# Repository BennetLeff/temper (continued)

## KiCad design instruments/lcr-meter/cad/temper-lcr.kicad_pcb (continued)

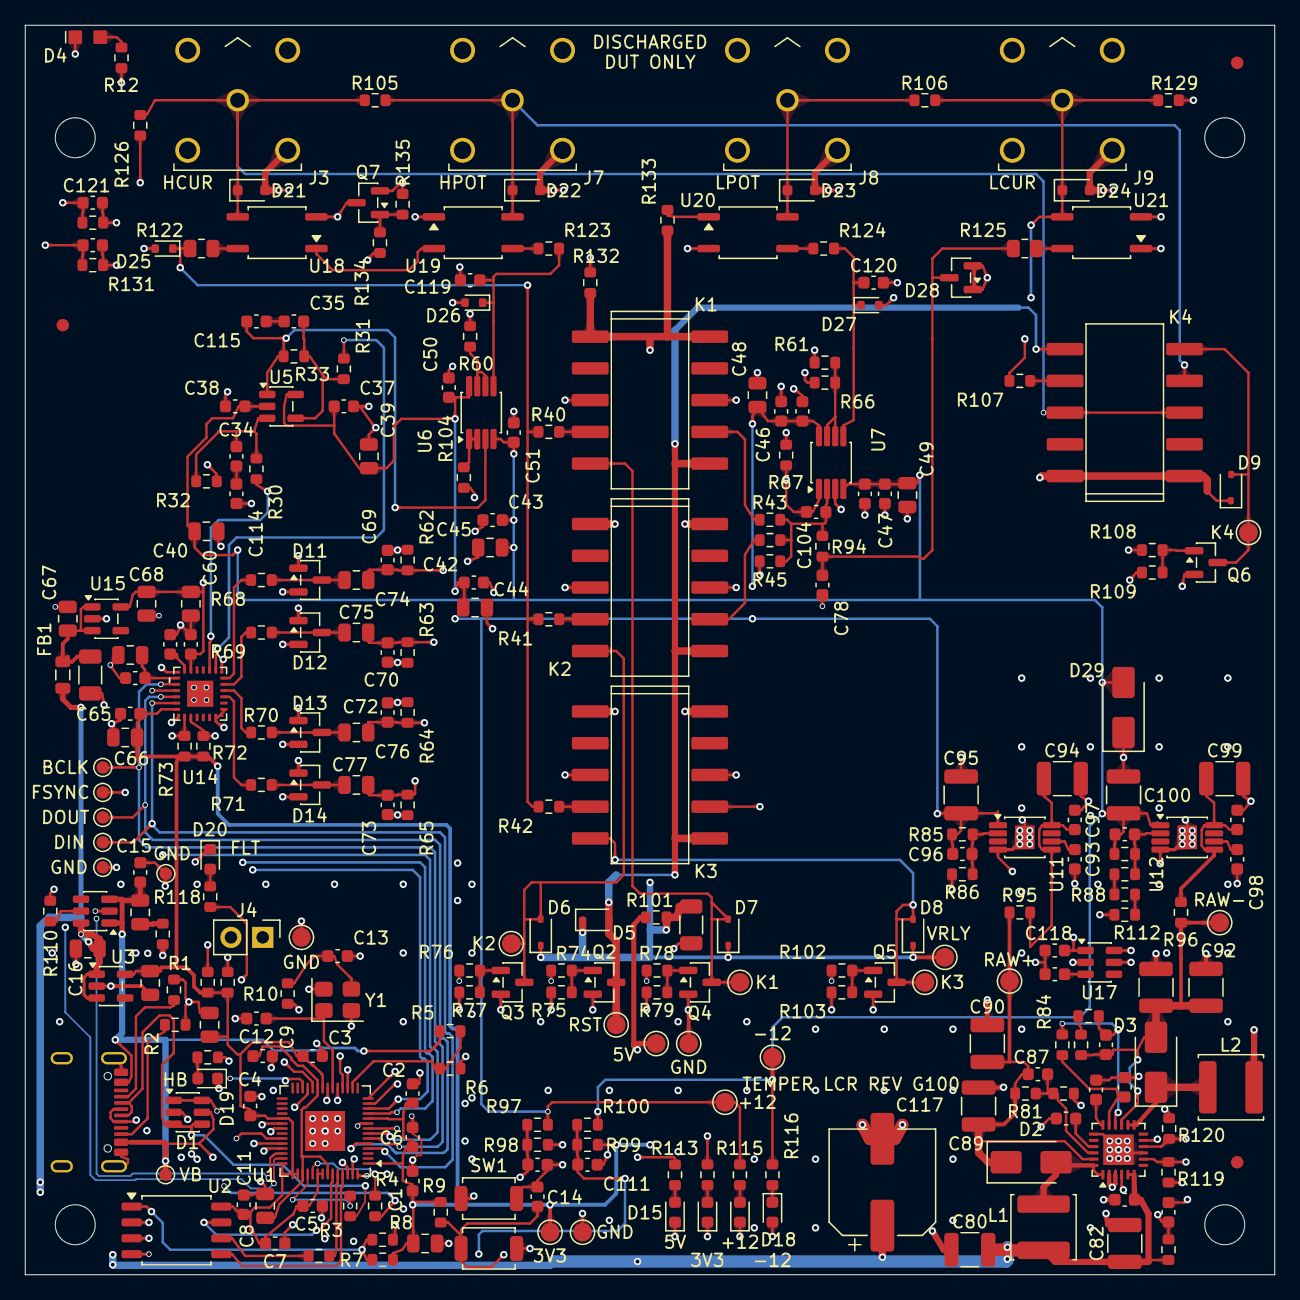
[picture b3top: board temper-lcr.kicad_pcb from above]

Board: 4 copper layers, 100.0 x 100.0 mm, 282 parts (0 on the bottom side), 143 nets.

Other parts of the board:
FID1, FID2, FID3: Fiducial_1mm_Mask2mm
H1, H2, H3, H4: MountingHole_3.2mm_M3
TP1: 5V; TestPoint_Pad_D1.5mm
TP2, TP9, TP22: GND; TestPoint_Pad_D1.5mm
TP3: +12; TestPoint_Pad_D1.5mm
TP4: -12; TestPoint_Pad_D1.5mm
TP5: VRLY; TestPoint_Pad_D1.5mm
TP6: RAW+; TestPoint_Pad_D1.5mm
TP7: RAW-; TestPoint_Pad_D1.5mm
TP8: 3V3; TestPoint_Pad_D1.5mm
TP10: K1; TestPoint_Pad_D1.5mm
TP11: K2; TestPoint_Pad_D1.5mm
TP12: K3; TestPoint_Pad_D1.5mm
TP13: K4; TestPoint_Pad_D1.5mm
TP14: RST; TestPoint_Pad_D1.5mm
TP15: BCLK; TestPoint_Pad_D1.0mm
TP16: FSYNC; TestPoint_Pad_D1.0mm
TP17: DOUT; TestPoint_Pad_D1.0mm
TP18: DIN; TestPoint_Pad_D1.0mm
TP19, TP21: GND; TestPoint_Pad_D1.0mm
TP20: VB; TestPoint_Pad_D1.0mm

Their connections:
3V3: TP8.1; also elsewhere on the board
5V: TP1.1; also elsewhere on the board
12V: TP3.1; also elsewhere on the board
-12V: TP4.1; also elsewhere on the board
GND: TP2.1, TP9.1, TP19.1, TP21.1, TP22.1; also elsewhere on the board
I2S_BCLK: TP15.1; also elsewhere on the board
I2S_DIN: TP18.1; also elsewhere on the board
I2S_DOUT: TP17.1; also elsewhere on the board
I2S_FSYNC: TP16.1; also elsewhere on the board
RAW_N: TP7.1; also elsewhere on the board
RAW_P: TP6.1; also elsewhere on the board
RLY_RST: TP14.1; also elsewhere on the board
RLY_SET_HI: TP12.1; also elsewhere on the board
RLY_SET_LO: TP10.1; also elsewhere on the board
RLY_SET_MED: TP11.1; also elsewhere on the board
RLY_SET_REF: TP13.1; also elsewhere on the board
USB_VBUS: TP20.1; also elsewhere on the board
VRLY: TP5.1; also elsewhere on the board

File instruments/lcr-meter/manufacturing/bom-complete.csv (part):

Designators,Quantity,Value,Manufacturer,MPN,LCSC,Footprint,Assembly,Catalog unit USD,Catalog subtotal USD
"C86,C93,C96,C98,C101,C50,C51,C52,C53",9,10nF 50V,FH (Guangdong Fenghua Advanced Tech),0603B103K500NT,C57112,Capacitor_SMD:C_0603_1608Metric,SMT,0.0101,0.0909
C88,1,4.7pF C0G,FH (Guangdong Fenghua Advanced Tech),0603CG4R7C500NT,C1669,Capacitor_SMD:C_0603_1608Metric,SMT,0.0054,0.0054
"R80,R76,R78,R102,R74,R108,R134",7,100R,UNI-ROYAL(Uniroyal Elec),0603WAF1000T5E,C22775,Resistor_SMD:R_0603_1608Metric,SMT,0.0026,0.0182
"R8,R10,R105,R106",4,1k,UNI-ROYAL(Uniroyal Elec),0603WAF1001T5E,C21190,Resistor_SMD:R_0603_1608Metric,SMT,0.003,0.012
"R7,R9,R98,R99",4,10k,UNI-ROYAL(Uniroyal Elec),0603WAF1002T5E,C25804,Resistor_SMD:R_0603_1608Metric,SMT,0.0054,0.0216
"R5,R6,R97,R77,R79,R103,R75,R109,R119,R120,R135",11,100k,UNI-ROYAL(Uniroyal Elec),0603WAF1003T5E,C25803,Resistor_SMD:R_0603_1608Metric,SMT,0.0031,0.0341
"R95,R96",2,1R,UNI-ROYAL(Uniroyal Elec),0603WAF100KT5E,C22936,Resistor_SMD:R_0603_1608Metric,SMT,0.0024,0.0048
"R84,R100",2,150k,UNI-ROYAL(Uniroyal Elec),0603WAF1503T5E,C22807,Resistor_SMD:R_0603_1608Metric,SMT,0.0017,0.0034
"R111,R126,R129",3,1.5M,UNI-ROYAL(Uniroyal Elec),0603WAF1504T5E,C4172,Resistor_SMD:R_0603_1608Metric,SMT,0.0019,0.0057
R121,1,1.5R,UNI-ROYAL(Uniroyal Elec),0603WAF150KT5E,C22769,Resistor_SMD:R_0603_1608Metric,SMT,0.0028,0.0028
"R110,R115,R116",3,24k 1%,UNI-ROYAL(Uniroyal Elec),0603WAF2402T5E,C23352,Resistor_SMD:R_0603_1608Metric,SMT,0.0024,0.0072
"R83,R127,R128,R130,R131",5,240k,UNI-ROYAL(Uniroyal Elec),0603WAF2403T5E,C4197,Resistor_SMD:R_0603_1608Metric,SMT,0.0018,0.009
"R132,R133",2,270R,UNI-ROYAL(Uniroyal Elec),0603WAF2700T5E,C22966,Resistor_SMD:R_0603_1608Metric,SMT,0.0017,0.0034
"R3,R4",2,27R,UNI-ROYAL(Uniroyal Elec),0603WAF270JT5E,C25190,Resistor_SMD:R_0603_1608Metric,SMT,0.0018,0.0036
"R114,R117,R118",3,3k,UNI-ROYAL(Uniroyal Elec),0603WAF3001T5E,C4211,Resistor_SMD:R_0603_1608Metric,SMT,0.0024,0.0072
R13,1,33R,UNI-ROYAL(Uniroyal Elec),0603WAF330JT5E,C23140,Resistor_SMD:R_0603_1608Metric,SMT,0.0024,0.0024
R101,1,0.33R,UNI-ROYAL(Uniroyal Elec),0603WAF330LT5E,C23410,Resistor_SMD:R_0603_1608Metric,SMT,0.0055,0.0055
R12,1,390,UNI-ROYAL(Uniroyal Elec),0603WAF3900T5E,C23151,Resistor_SMD:R_0603_1608Metric,SMT,0.0017,0.0017
R82,1,40.2k,UNI-ROYAL(Uniroyal Elec),0603WAF4022T5E,C12447,Resistor_SMD:R_0603_1608Metric,SMT,0.0021,0.0021
R81,1,430k,UNI-ROYAL(Uniroyal Elec),0603WAF4303T5E,C25969,Resistor_SMD:R_0603_1608Metric,SMT,0.0031,0.0031
"R68,R69,R70,R71",4,470R,UNI-ROYAL(Uniroyal Elec),0603WAF4700T5E,C23179,Resistor_SMD:R_0603_1608Metric,SMT,0.002,0.008
"R72,R73",2,4.7k,UNI-ROYAL(Uniroyal Elec),0603WAF4701T5E,C23162,Resistor_SMD:R_0603_1608Metric,SMT,0.002,0.004
R104,1,47R,UNI-ROYAL(Uniroyal Elec),0603WAF470JT5E,C23182,Resistor_SMD:R_0603_1608Metric,SMT,0.002,0.002
"R1,R2,R113",3,5.1k,UNI-ROYAL(Uniroyal Elec),0603WAF5101T5E,C23186,Resistor_SMD:R_0603_1608Metric,SMT,0.0015,0.0045
R85,1,82k,UNI-ROYAL(Uniroyal Elec),0603WAF8202T5E,C23254,Resistor_SMD:R_0603_1608Metric,SMT,0.0027,0.0027
R86,1,9.1k,UNI-ROYAL(Uniroyal Elec),0603WAF9101T5E,C23260,Resistor_SMD:R_0603_1608Metric,SMT,0.0031,0.0031
"D6,D7,D8,D5,D9",5,1N4148WS,"Jiangsu Changjing Electronics Technology Co., Ltd.",1N4148WS,C2128,Diode_SMD:D_SOD-323,SMT,0.0143,0.0715
Y1,1,12MHz CL10pF,Abracon LLC,ABM8-272-T3,C20625731,Crystal:Crystal_SMD_3225-4Pin_3.2x2.5mm,SMT,0.6471,0.6471
"Q3,Q4,Q5,Q2,Q6,Q7",6,AO3400A,Alpha & Omega Semicon,AO3400A,C20917,Package_TO_SOT_SMD:SOT-23,SMT,0.0973,0.5838
"U3,U15",2,3.3V AP2112K,Diodes Incorporated,AP2112K-3.3TRG1,C51118,Package_TO_SOT_SMD:SOT-23-5,SMT,0.1772,0.3544
"R33,R32",2,2k 0.1%,Viking Tech,AR03BTCX2001,C318130,Resistor_SMD:R_0603_1608Metric,SMT,0.0364,0.0728
"R41,R44,R89,R112",4,5k 0.1%,Viking Tech,AR03BTCX5001,C2828621,Resistor_SMD:R_0603_1608Metric,SMT,0.0318,0.1272
"D11,D12,D13,D14",4,BAT54S,hongjiacheng,BAT54S,C7420333,Package_TO_SOT_SMD:SOT-23,SMT,0.0129,0.0516
D28,1,BAV99,Nexperia,"BAV99,215",C2500,Package_TO_SOT_SMD:SOT-23,SMT,0.0111,0.0111
"J3,J7,J8,J9",4,BNC HCUR,SAMZO,BNC-KYWE-295-W4-N,C41416668,LCR:BNC_SAMZO_KYWE-295-W4-N_Horizontal,Hand fit,1.29,5.16
"C119,C120",2,1nF C0G,Yageo,CC0603JRNPO9BN102,C106246,Capacitor_SMD:C_0603_1608Metric,SMT,0.0066,0.0132
C85,1,4.7nF 50V C0G,YAGEO,CC0603JRNPO9BN472,C576818,Capacitor_SMD:C_0603_1608Metric,SMT,0.0285,0.0285
"C34,C114,C35,C115,C69,C70,C72,C73",8,560pF C0G 5%,YAGEO,CC0603JRNPO9BN561,C107054,Capacitor_SMD:C_0603_1608Metric,SMT,0.0066,0.0528
"C1,C2,C3,C4,C6,C7,C9,C11,C14,C15,C37,C38,C42,C43,C46,C47,C81,C83,C97,C102,C110,C111,C61,C63,C65,C116,C118,C121,C122",29,100nF 50V,YAGEO,CC0603KRX7R9BB104,C14663,Capacitor_SMD:C_0603_1608Metric,SMT,0.0084,0.2436
"C39,C40,C44,C45,C48,C49",6,2.2uF 50V X7R,YAGEO,CC0805KKX7R9BB225,C125847,Capacitor_SMD:C_0805_2012Metric,SMT,0.1143,0.6858
C5,1,1uF 50V X5R,Samsung Electro-Mechanics,CL10A105KB8NNNC,C15849,Capacitor_SMD:C_0603_1608Metric,SMT,0.0153,0.0153
C62,1,2.2uF 16V X5R,Samsung Electro-Mechanics,CL10A225KO8NNNC,C23630,Capacitor_SMD:C_0603_1608Metric,SMT,0.0119,0.0119
C84,1,220nF 25V,Samsung Electro-Mechanics,CL10B224KA8NNNC,C21120,Capacitor_SMD:C_0603_1608Metric,SMT,0.0097,0.0097
"C104,C78",2,100pF C0G 5%,Samsung Electro-Mechanics,CL10C101JB8NNNC,C14858,Capacitor_SMD:C_0603_1608Metric,SMT,0.0086,0.0172
"C12,C13,C87",3,15pF C0G,Samsung Electro-Mechanics,CL10C150JB8NNNC,C1644,Capacitor_SMD:C_0603_1608Metric,SMT,0.0111,0.0333
"C18,C60,C64,C66",4,10uF 25V X5R,Samsung Electro-Mechanics,CL21A106KAYNNNE,C15850,Capacitor_SMD:C_0805_2012Metric,SMT,0.0773,0.3092
C113,1,4.7uF 25V X5R,Samsung Electro-Mechanics,CL21A475KAQNNNE,C1779,Capacitor_SMD:C_0805_2012Metric,SMT,0.0343,0.0343
"C8,C10,C16,C17,C67,C68,C74,C75,C76,C77",10,1uF 50V,Samsung Electro-Mechanics,CL21B105KBFNNNE,C28323,Capacitor_SMD:C_0805_2012Metric,SMT,0.0344,0.344
"C103,C112",2,22uF 25V X5R,Samsung Electro-Mechanics,CL31A226KAHNNNE,C12891,Capacitor_SMD:C_1206_3216Metric,SMT,0.1798,0.3596
"C80,C82,C89,C90,C91,C92,C94,C95,C99,C100",10,10uF 50V X7R,Samsung Electro-Mechanics,CL32B106KBJNNNE,C138687,Capacitor_SMD:C_1210_3225Metric,SMT,0.33,3.3
"R123,R124",2,100R,Vishay Draloric,CRCW0603100RFKEAHP,C844725,Resistor_SMD:R_0603_1608Metric,SMT,0.028,0.056
"R122,R125",2,10R,Vishay Draloric,CRCW080510R0FKEAHP,C844598,Resistor_SMD:R_0805_2012Metric,SMT,0.0359,0.0718
"L1,L2",2,4.7uH 3.8A shielded,cjiang (Changjiang Microelectronics Tech),FNR5040S4R7MT,C167963,Inductor_SMD:L_Changjiang_FNR5040S,SMT,0.0621,0.1242
U2,1,GD25Q16ESIGR,GigaDevice,GD25Q16ESIGR,C2922792,Package_SO:SOIC-8_5.3x5.3mm_P1.27mm,SMT,0.6011,0.6011
FB1,1,100R@100MHz 800mA,Sunlord,GZ2012D101TF,C1015,Inductor_SMD:L_0805_2012Metric,SMT,0.0311,0.0311
"D25,D26,D27",3,H3V3LD5B,Zhuhai Hongjiacheng (HJC),H3V3LD5B,C20615817,Diode_SMD:D_SOD-523,SMT,0.0192,0.0576
"D21,D22,D23,D24",4,H4V5HD3B,Zhuhai Hongjiacheng (HJC),H4V5HD3B,C20615803,LCR:D_SOD-323_HJC,SMT,0.0373,0.1492
"D15,D16,D17,D18,D19,D20",6,RED,Hubei KENTO Elec,KT-0603R,C2286,LED_SMD:LED_0603_1608Metric,SMT,0.0073,0.0438
U17,1,LM3880-1AA,Texas Instruments,LM3880MF-1AA/NOPB,C486059,Package_TO_SOT_SMD:SOT-23-6,SMT,1.8617,1.8617
D4,1,ORANGE,Lite-On,LTST-S270KFKT,C160472,LCR:LED_LiteOn_LTST-S270KFKT_SideView,SMT,0.0382,0.0382
U5,1,OPA197IDBVR,Texas Instruments,OPA197IDBVR,C221351,Package_TO_SOT_SMD:SOT-23-5,SMT,0.5978,0.5978
"U6,U7",2,OPA2810IDGKR,Texas Instruments,OPA2810IDGKR,C2864204,Package_SO:VSSOP-8_3x3mm_P0.65mm,SMT,5.09,10.18
C117,1,330uF 10V polymer,Nichicon,PCG1A331MCL1GS,C433208,Capacitor_SMD:CP_Elec_8x6.9,SMT,1.1292,1.1292
U1,1,RP2040,Raspberry Pi,RP2040,C2040,Package_DFN_QFN:QFN-56-1EP_7x7mm_P0.4mm_EP3.2x3.2mm,SMT,1.0752,1.0752
"R42,R45,R87",3,100k 0.1%,YAGEO,RT0603BRD07100KL,C122538,Resistor_SMD:R_0603_1608Metric,SMT,0.0322,0.0966
"R40,R43",2,100R 0.1%,YAGEO,RT0603BRD07100RL,C122970,Resistor_SMD:R_0603_1608Metric,SMT,0.0319,0.0638
"R88,R60,R61,R66,R67,R62,R63,R64,R65,R107",10,1k 0.1%,YAGEO,RT0603BRD071KL,C110776,Resistor_SMD:R_0603_1608Metric,SMT,0.0313,0.313
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
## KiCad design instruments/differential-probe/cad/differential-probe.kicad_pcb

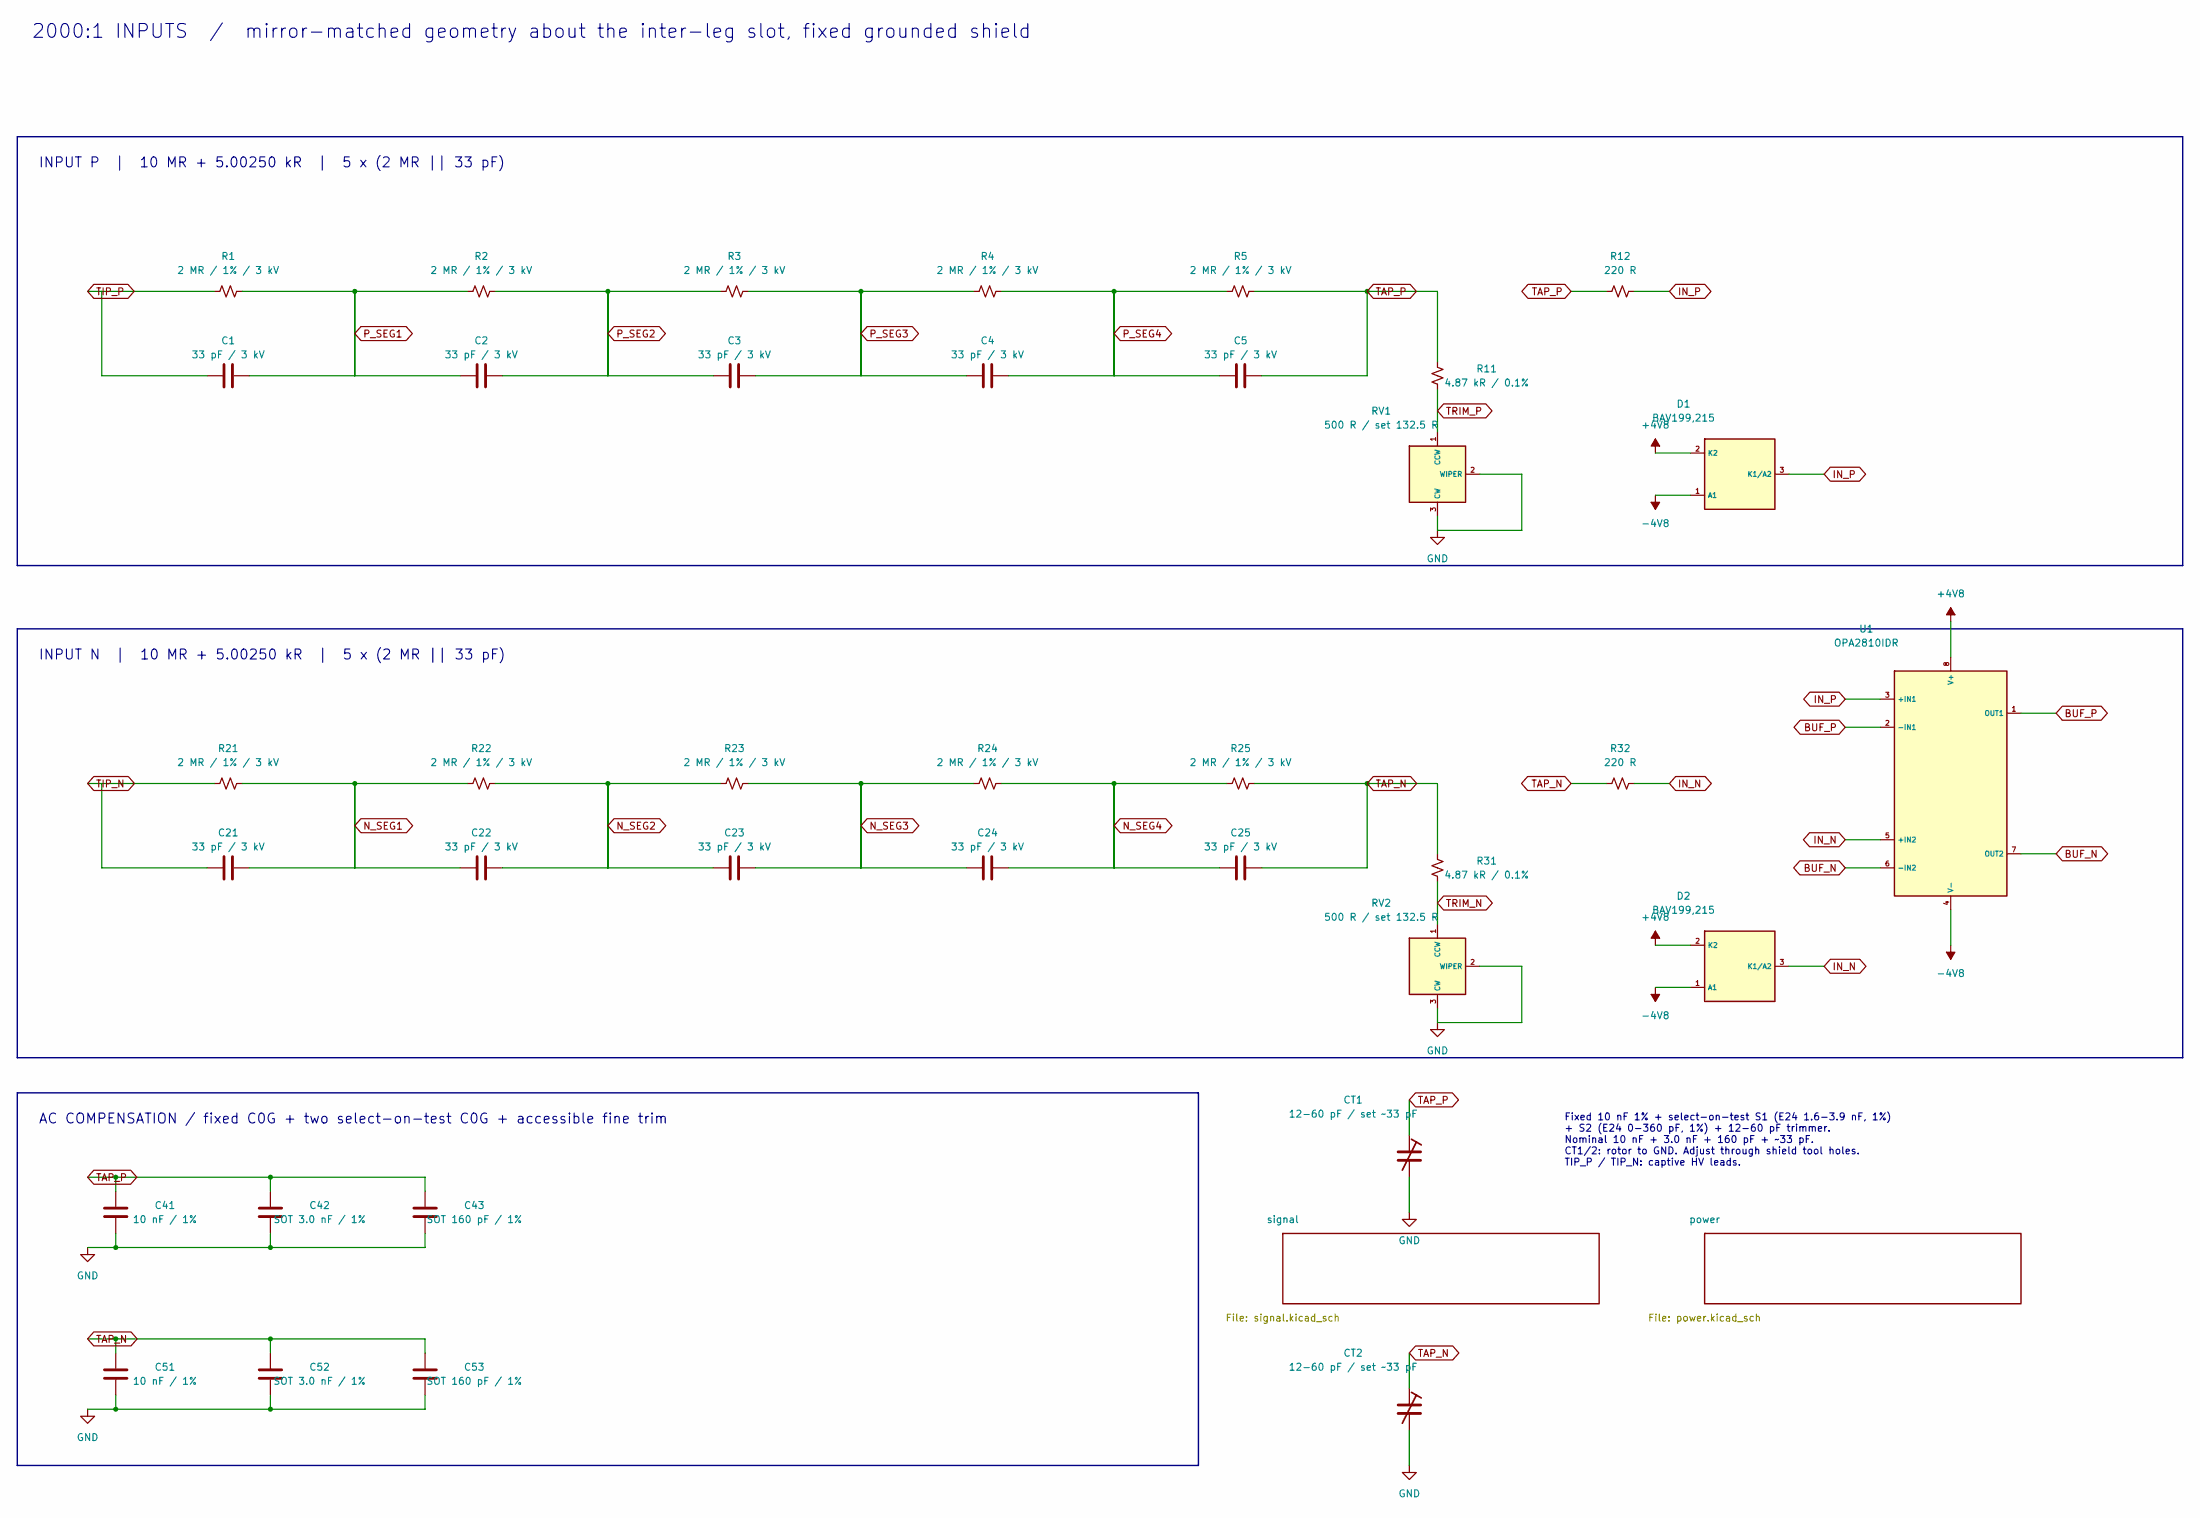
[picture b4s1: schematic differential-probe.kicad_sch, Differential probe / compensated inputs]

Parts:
C1, C2, C3, C4, C5, C21, C22, C23, C24, C25: 33 pF / 3 kV; C_1812_HV_Slot; MPN CC1812JKNPOEBN330; LCSC C2359543
C41, C51: 10 nF / 1%; C_1206_3216Metric; MPN CC1206FKNPO9BN103; LCSC C541597
C42, C52: SOT 3.0 nF / 1%; C_0805_2012Metric; MPN C0805C302F5GACTU
C43, C53: SOT 160 pF / 1%; C_0805_2012Metric; MPN C0805C161F5GACTU
CT1, CT2: 12-60 pF / set ~33 pF; GKG60015_TopAdjust; MPN GKG60015
D1, D2: BAV199,215; SOT-23; MPN BAV199,215; LCSC C40919
R1, R2, R3, R4, R5, R21, R22, R23, R24, R25: 2 MR / 1% / 3 kV; R_2512_6332Metric; MPN HV121WF2004T4E; LCSC C2779442
R11, R31: 4.87 kR / 0.1%; R_0603_1608Metric; MPN RT0603BRD074K87L; LCSC C861446
R12, R32: 220 R; R_0805_2012Metric; MPN 0805W8F2200T5E; LCSC C17557
RV1, RV2: 500 R / set 132.5 R; Potentiometer_Bourns_3296W_Vertical; MPN 3296W-1-501LF; LCSC C69564
U1: OPA2810IDR; SOIC-8_3.9x4.9mm_P1.27mm; MPN OPA2810IDR; LCSC C1849413

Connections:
+4V8: D1.2 (K2), D2.2 (K2), U1.8 (V+); also elsewhere on the board
-4V8: D1.1 (A1), D2.1 (A1), U1.4 (V-); also elsewhere on the board
BUF_N: U1.6 (-IN2), U1.7 (OUT2); also elsewhere on the board
BUF_P: U1.1 (OUT1), U1.2 (-IN1); also elsewhere on the board
GND: C41.2, C42.2, C43.2, C51.2, C52.2, C53.2, CT1.2, CT2.2, RV1.2 (WIPER), RV1.3 (CW), RV2.2 (WIPER), RV2.3 (CW); also elsewhere on the board
IN_N: D2.3 (K1/A2), R32.2, U1.5 (+IN2)
IN_P: D1.3 (K1/A2), R12.2, U1.3 (+IN1)
N_SEG1: C21.2, C22.1, R21.2, R22.1
N_SEG2: C22.2, C23.1, R22.2, R23.1
N_SEG3: C23.2, C24.1, R23.2, R24.1
N_SEG4: C24.2, C25.1, R24.2, R25.1
P_SEG1: C1.2, C2.1, R1.2, R2.1
P_SEG2: C2.2, C3.1, R2.2, R3.1
P_SEG3: C3.2, C4.1, R3.2, R4.1
P_SEG4: C4.2, C5.1, R4.2, R5.1
TAP_N: C25.2, C51.1, C52.1, C53.1, CT2.1, R25.2, R31.1, R32.1
TAP_P: C5.2, C41.1, C42.1, C43.1, CT1.1, R5.2, R11.1, R12.1
TIP_N: C21.1, R21.1; also elsewhere on the board
TIP_P: C1.1, R1.1; also elsewhere on the board
TRIM_N: R31.2, RV2.1 (CCW)
TRIM_P: R11.2, RV1.1 (CCW)

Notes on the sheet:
2000:1 INPUTS / mirror-matched geometry about the inter-leg slot, fixed grounded shield
INPUT P | 10 MR + 5.00250 kR | 5 x (2 MR || 33 pF)
INPUT N | 10 MR + 5.00250 kR | 5 x (2 MR || 33 pF)
AC COMPENSATION / fixed C0G + two select-on-test C0G + accessible fine trim
Fixed 10 nF 1% + select-on-test S1 (E24 1.6-3.9 nF, 1%) + S2 (E24 0-360 pF, 1%) + 12-60 pF trimmer. Nominal 10 nF + 3.0 nF + 160 pF + ~33 pF. CT1/2: rotor to GND. Adjust through shield tool holes. TIP_P / TIP_N: captive HV leads.

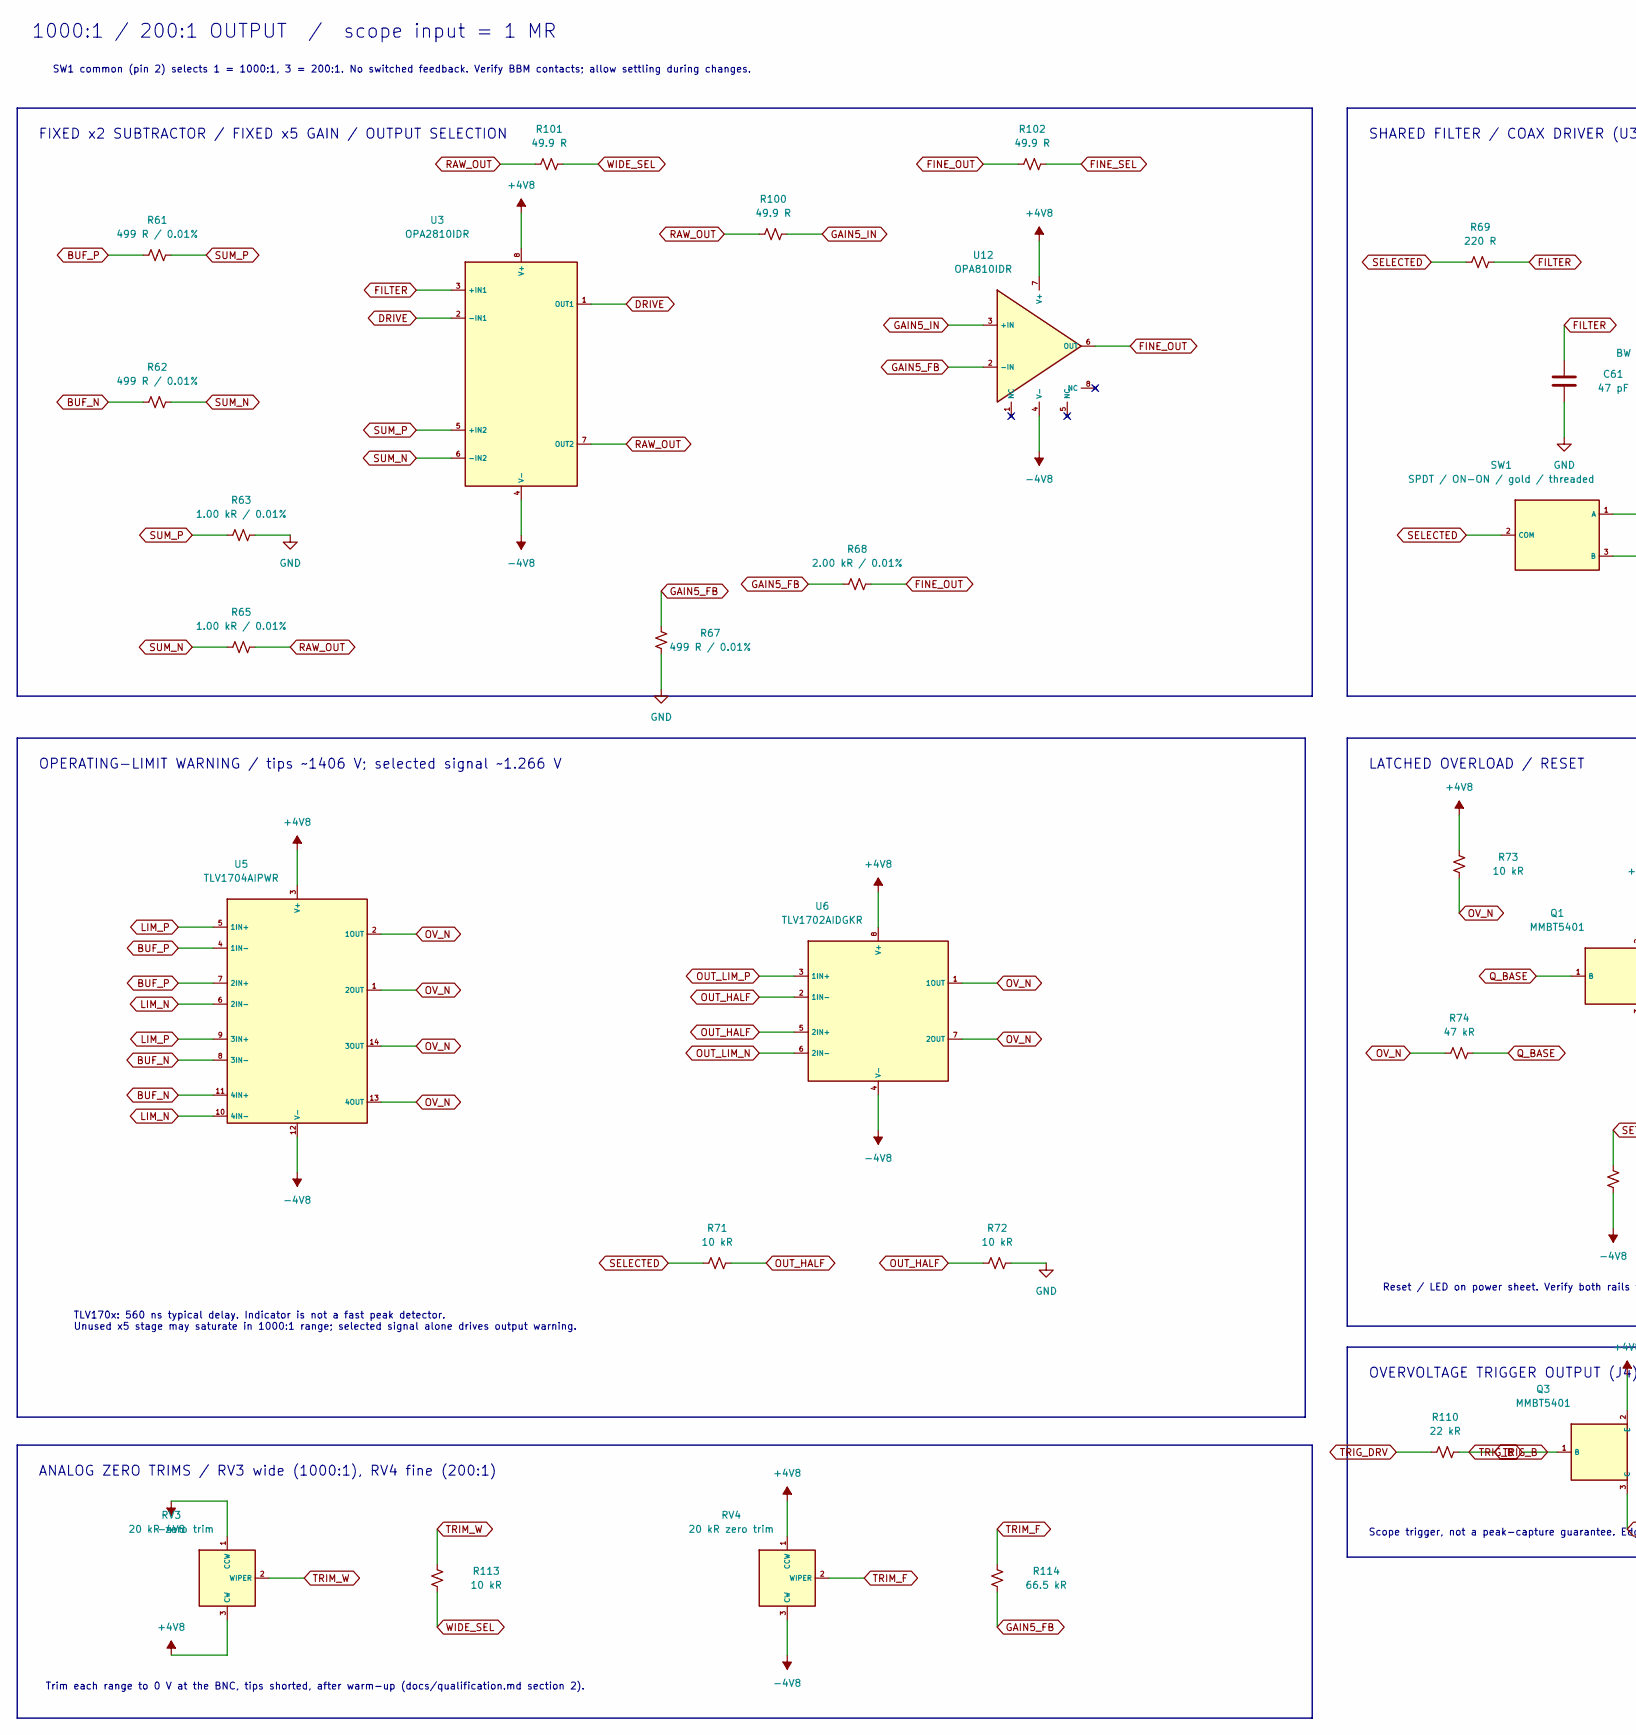
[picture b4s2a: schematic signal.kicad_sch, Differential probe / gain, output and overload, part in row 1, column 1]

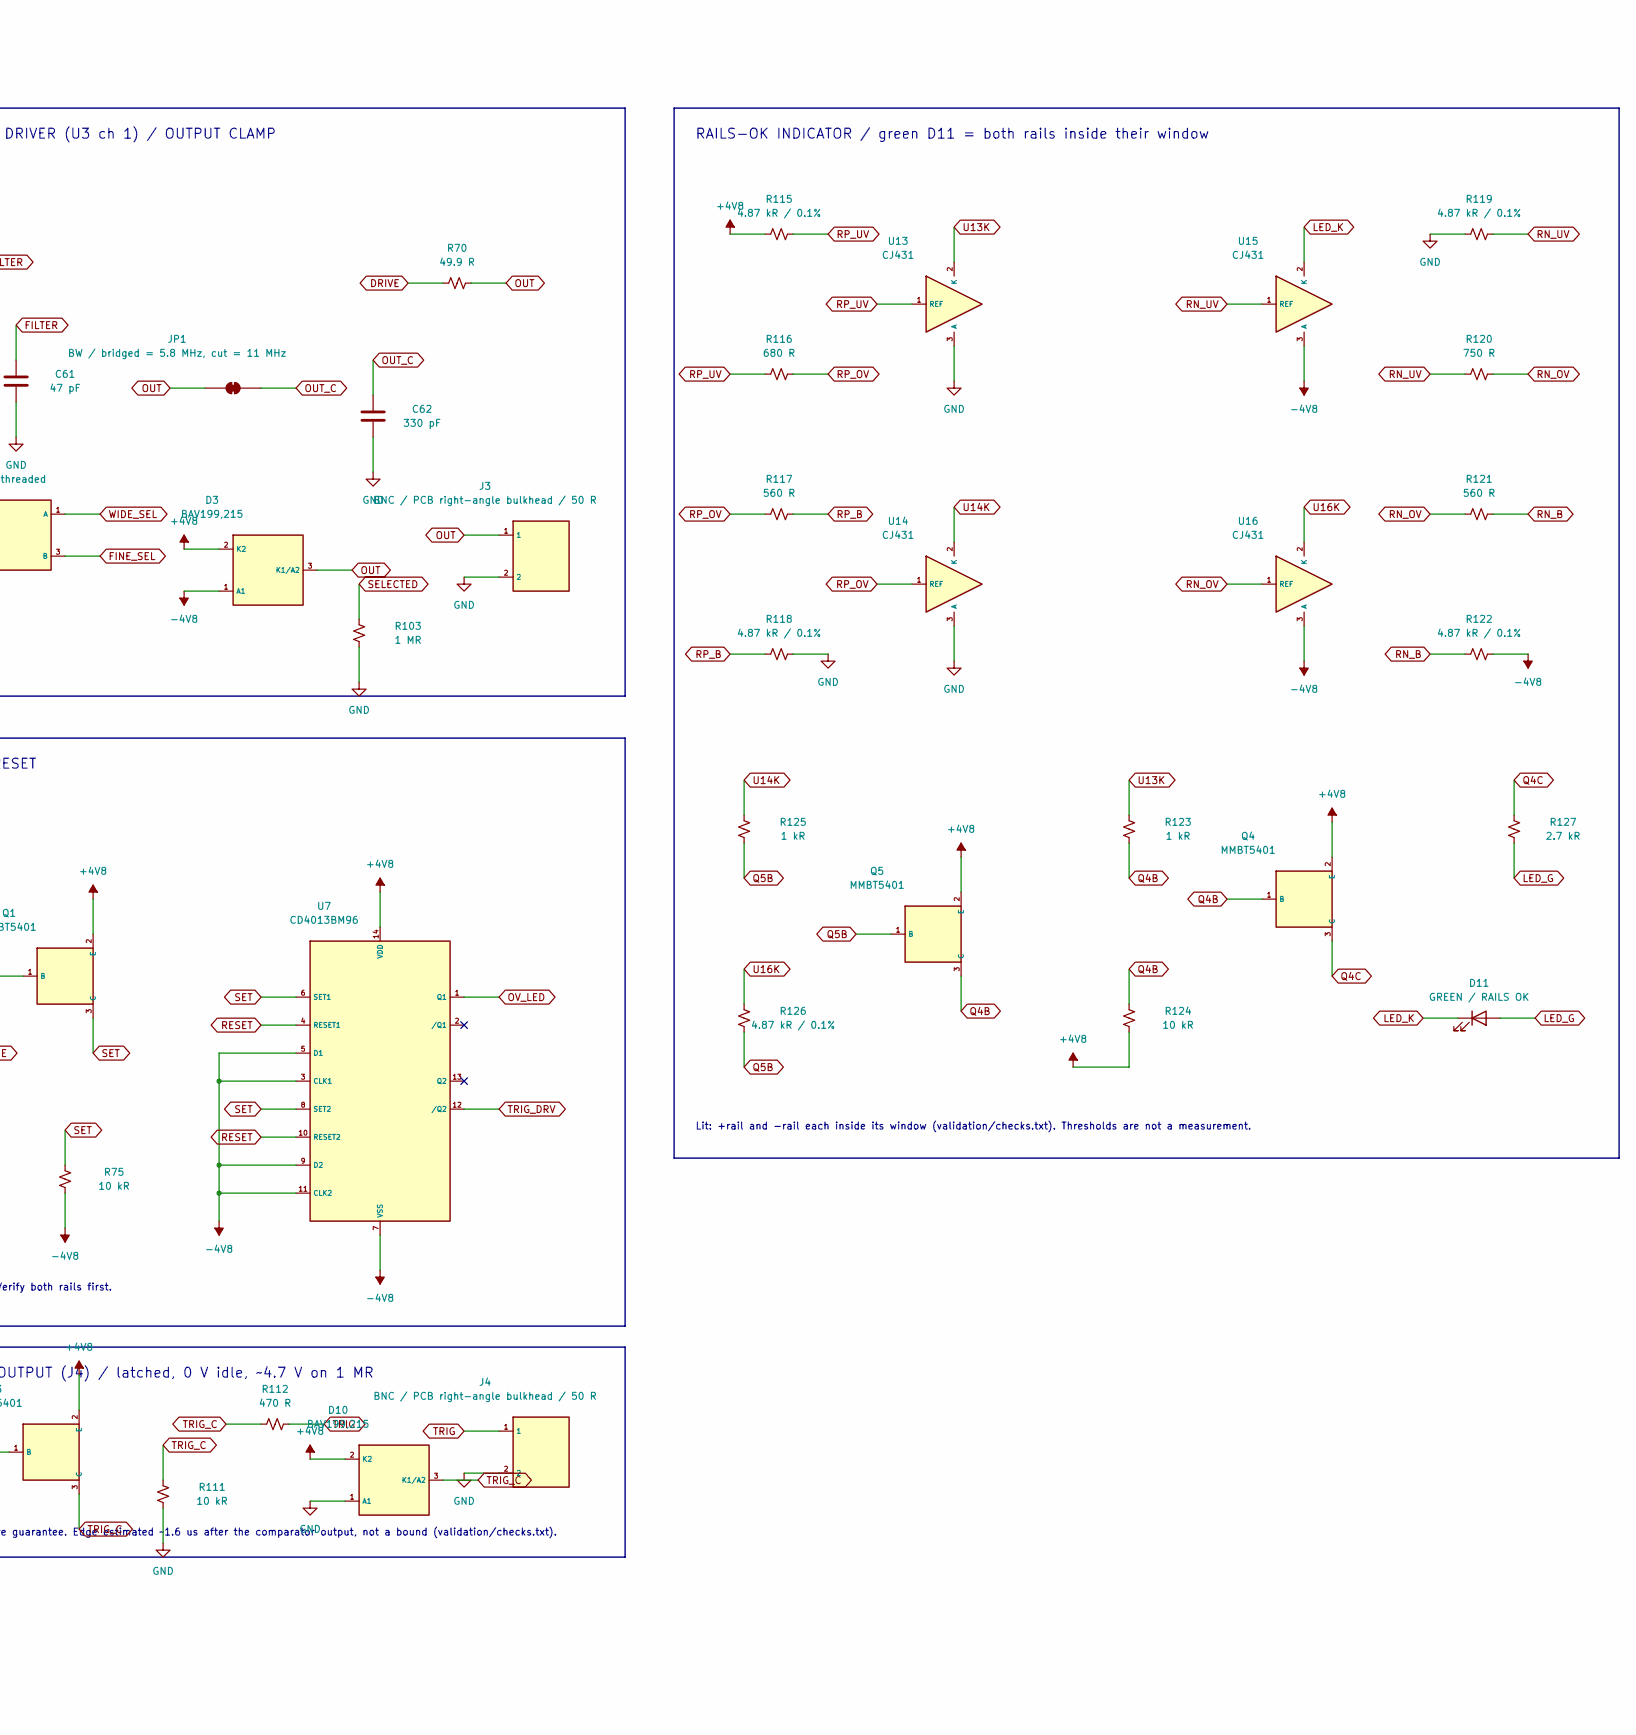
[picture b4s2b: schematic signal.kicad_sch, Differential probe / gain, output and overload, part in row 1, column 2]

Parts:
C61: 47 pF; C_0805_2012Metric; MPN CL21C470JBANNNC; LCSC C14857
C62: 330 pF; C_0603_1608Metric; MPN CL10C331JB8NNNC; LCSC C1664
D3, D10: BAV199,215; SOT-23; MPN BAV199,215; LCSC C40919
D11: GREEN / RAILS OK; LED_0805_2012Metric; MPN KT-0805G; LCSC C2297
J3, J4: BNC / PCB right-angle bulkhead / 50 R; BNC_Amphenol_031-5431_Horizontal; MPN 031-5431-10RFX; LCSC C6956217
JP1: BW / bridged = 5.8 MHz, cut = 11 MHz; SolderJumper-2_P1.3mm_Bridged_RoundedPad1.0x1.5mm; MPN PCB copper (solder jumper)
Q1, Q3, Q4, Q5: MMBT5401; SOT-23; MPN MMBT5401; LCSC C8326
R61, R62, R67: 499 R / 0.01%; R_0603_1608Metric; MPN RNCF0603TKY499R
R63, R65: 1.00 kR / 0.01%; R_0603_1608Metric; MPN RNCF0603TKY1K00
R68: 2.00 kR / 0.01%; R_0603_1608Metric; MPN RNCF0603TKY2K00
R69: 220 R; R_0805_2012Metric; MPN 0805W8F2200T5E; LCSC C17557
R70, R100, R101, R102: 49.9 R; R_0805_2012Metric; MPN 0805W8F499JT5E; LCSC C17720
R71, R72, R73, R75, R111, R113, R124: 10 kR; R_0805_2012Metric; MPN RT0805BRD0710KL
R74: 47 kR; R_0805_2012Metric; MPN 0805W8F4702T5E; LCSC C17713
R103: 1 MR; R_0805_2012Metric; MPN 0805W8F1004T5E; LCSC C17514
R110: 22 kR; R_0805_2012Metric; MPN 0805W8F2202T5E; LCSC C17560
R112: 470 R; R_0805_2012Metric; MPN 0805W8F4700T5E; LCSC C17710
R114: 66.5 kR; R_0805_2012Metric; MPN RT0805BRD0766K5L
R115, R118, R119, R122, R126: 4.87 kR / 0.1%; R_0603_1608Metric; MPN RT0603BRD074K87L; LCSC C861446
R116: 680 R; R_0805_2012Metric; MPN 0805W8F6800T5E; LCSC C17798
R117, R121: 560 R; R_0805_2012Metric; MPN 0805W8F5600T5E; LCSC C28636
R120: 750 R; R_0805_2012Metric; MPN 0805W8F7500T5E; LCSC C17818
R123, R125: 1 kR; R_0805_2012Metric; MPN 0805W8F1001T5E; LCSC C17513
R127: 2.7 kR; R_0805_2012Metric; MPN 0805W8F2701T5E; LCSC C17530
RV3, RV4: 20 kR zero trim; Potentiometer_Bourns_3296W_Vertical; MPN 3296W-1-203LF; LCSC C34845
SW1: SPDT / ON-ON / gold / threaded; ESwitch_100_M7_SPDT; MPN 100SP1T1B5M7RE
U3: OPA2810IDR; SOIC-8_3.9x4.9mm_P1.27mm; MPN OPA2810IDR; LCSC C1849413
U5: TLV1704AIPWR; TSSOP-14_4.4x5mm_P0.65mm; MPN TLV1704AIPWR; LCSC C181596
U6: TLV1702AIDGKR; VSSOP-8_3x3mm_P0.65mm; MPN TLV1702AIDGKR; LCSC C2870937
U7: CD4013BM96; SOIC-14_3.9x8.7mm_P1.27mm; MPN CD4013BM96; LCSC C13527
U12: OPA810IDR; SOIC-8_3.9x4.9mm_P1.27mm; MPN OPA810IDR; LCSC C1852077
U13, U14, U15, U16: CJ431; SOT-23; MPN CJ431; LCSC C3113

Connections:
+4V8: D3.2 (K2), D10.2 (K2), Q1.2 (E), Q3.2 (E), Q4.2 (E), Q5.2 (E), R73.1, R115.1, R124.2, RV3.3 (CW), RV4.1 (CCW), U3.8 (V+), U5.3 (V+), U6.8 (V+), U7.14 (VDD), U12.7 (V+); also elsewhere on the board
-4V8: D3.1 (A1), R75.2, R122.2, RV3.1 (CCW), RV4.3 (CW), U3.4 (V-), U5.12 (V-), U6.4 (V-), U7.3 (CLK1), U7.5 (D1), U7.7 (VSS), U7.9 (D2), U7.11 (CLK2), U12.4 (V-), U15.3 (A), U16.3 (A); also elsewhere on the board
BUF_N: R62.1, U5.8 (3IN-), U5.11 (4IN+); also elsewhere on the board
BUF_P: R61.1, U5.4 (1IN-), U5.7 (2IN+); also elsewhere on the board
DRIVE: R70.1, U3.1 (OUT1), U3.2 (-IN1)
FILTER: C61.1, R69.2, U3.3 (+IN1)
FINE_OUT: R68.2, R102.1, U12.6 (OUT)
FINE_SEL: R102.2, SW1.3 (B)
GAIN5_FB: R67.1, R68.1, R114.2, U12.2 (-IN)
GAIN5_IN: R100.2, U12.3 (+IN)
GND: C61.2, C62.2, D10.1 (A1), J3.2, J4.2, R63.2, R67.2, R72.2, R103.2, R111.2, R118.2, R119.1, U13.3 (A), U14.3 (A); also elsewhere on the board
LED_G: D11.2 (A), R127.2
LED_K: D11.1 (K), U15.2 (K)
LIM_N: U5.6 (2IN-), U5.10 (4IN-); also elsewhere on the board
LIM_P: U5.5 (1IN+), U5.9 (3IN+); also elsewhere on the board
OUT: D3.3 (K1/A2), J3.1, JP1.1 (A), R70.2
OUT_C: C62.1, JP1.2 (B)
OUT_HALF: R71.2, R72.1, U6.2 (1IN-), U6.5 (2IN+)
OUT_LIM_N: U6.6 (2IN-); also elsewhere on the board
OUT_LIM_P: U6.3 (1IN+); also elsewhere on the board
OV_LED: U7.1 (Q1); also elsewhere on the board
OV_N: R73.2, R74.1, U5.1 (2OUT), U5.2 (1OUT), U5.13 (4OUT), U5.14 (3OUT), U6.1 (1OUT), U6.7 (2OUT)
Q4B: Q4.1 (B), Q5.3 (C), R123.2, R124.1
Q4C: Q4.3 (C), R127.1
Q5B: Q5.1 (B), R125.2, R126.2
Q_BASE: Q1.1 (B), R74.2
RAW_OUT: R65.2, R100.1, R101.1, U3.7 (OUT2)
RESET: U7.4 (RESET1), U7.10 (RESET2); also elsewhere on the board
RN_B: R121.2, R122.1
RN_OV: R120.2, R121.1, U16.1 (REF)
RN_UV: R119.2, R120.1, U15.1 (REF)
RP_B: R117.2, R118.1
RP_OV: R116.2, R117.1, U14.1 (REF)
RP_UV: R115.2, R116.1, U13.1 (REF)
SELECTED: R69.1, R71.1, R103.1, SW1.2 (COM)
SET: Q1.3 (C), R75.1, U7.6 (SET1), U7.8 (SET2)
SUM_N: R62.2, R65.1, U3.6 (-IN2)
SUM_P: R61.2, R63.1, U3.5 (+IN2)
TRIG: J4.1, R112.2
TRIG_B: Q3.1 (B), R110.2
TRIG_C: D10.3 (K1/A2), Q3.3 (C), R111.1, R112.1
TRIG_DRV: R110.1, U7.12 (/Q2)
TRIM_F: R114.1, RV4.2 (WIPER)
TRIM_W: R113.1, RV3.2 (WIPER)
U13K: R123.1, U13.2 (K)
U14K: R125.1, U14.2 (K)
U16K: R126.1, U16.2 (K)
WIDE_SEL: R101.2, R113.2, SW1.1 (A)

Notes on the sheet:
1000:1 / 200:1 OUTPUT / scope input = 1 MR
FIXED x2 SUBTRACTOR / FIXED x5 GAIN / OUTPUT SELECTION
SW1 common (pin 2) selects 1 = 1000:1, 3 = 200:1. No switched feedback. Verify BBM contacts; allow settling during changes.
SHARED FILTER / COAX DRIVER (U3 ch 1) / OUTPUT CLAMP
OPERATING-LIMIT WARNING / tips ~1406 V; selected signal ~1.266 V
TLV170x: 560 ns typical delay. Indicator is not a fast peak detector. Unused x5 stage may saturate in 1000:1 range; selected signal alone drives output warning.
LATCHED OVERLOAD / RESET
Reset / LED on power sheet. Verify both rails first.
OVERVOLTAGE TRIGGER OUTPUT (J4) / latched, 0 V idle, ~4.7 V on 1 MR
Scope trigger, not a peak-capture guarantee. Edge estimated ~1.6 us after the comparator output, not a bound (validation/checks.txt).
ANALOG ZERO TRIMS / RV3 wide (1000:1), RV4 fine (200:1)
Trim each range to 0 V at the BNC, tips shorted, after warm-up (docs/qualification.md section 2).
RAILS-OK INDICATOR / green D11 = both rails inside their window
Lit: +rail and -rail each inside its window (validation/checks.txt). Thresholds are not a measurement.
